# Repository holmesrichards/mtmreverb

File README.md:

# Spring Reverb

This is a Kosmo format adaptation of the [Music Thing Modular Spring Reverb](https://www.musicthing.co.uk/Spring-Reverb/). (Which is open source, [Creative Commons Attribution-ShareAlike 3.0](https://creativecommons.org/licenses/by-sa/3.0/), so this project is too.)

# Circuit changes

Only very minor tweaks to the original circuit:

* Expansion module (consisting of a potentiometer and a pair of RCA jacks) incorporated into main module
* Single rail-to-rail bypass caps replaced with dual rail-to-ground
* Power reversal protection diodes added
* AC coupling capacitors C1, C2 changed from 10 µF electrolytic to 1 µF film
* Footprint for 100k resistor to ground on IN_2 (FEEDBACK) left in place but marked "OMIT?"

# Discussion

R5, the 100k to ground on input IN_2, is parallel to several other ~50k resistances to ground. This means the input impedance at IN_2 is much lower than the usual 100k. R5 only makes it even lower, and I see no reason why one would want to do that. I left the footprint for this resistor in place but marked it "OMIT?" on the silkscreen and left it out in my build. This resistor is not included in the BOM.

# Errata

* In the v1.0 circuit boards the solder jumper is bridged, not open, so it should be cut if using the brick and left alone if not (contrary to what the silkscreen implies). 

* In the v1.0 front panel the pads around the hole for the "To" phono jack make the jack contact ground. This is incorrect. Use nylon washers on both sides of the hole to isolate the jack, and make sure the hole isn't plated through. 

These errors are corrected in the post-v1.0 versions.

## Current draw

 mA +12 V,  mA -12 V
 
## Photos

## Documentation

* [Schematic](Docs/springReverbRev2_schematic.pdf)
* PCB layout: [front board front side](Docs/Layout/springReverbRev2_FrontPCB/springReverbRev2_FrontPCB_front.svg), [front board back side](Docs/Layout/springReverbRev2_FrontPCB/springReverbRev2_FrontPCB_back.svg), [back board front side](Docs/Layout/springReverbRev2_BackPCB/springReverbRev2_BackPCB_front.svg), [back board back side](Docs/Layout/springReverbRev2_BackPCB/springReverbRev2_BackPCB_back.svg)
* [BOM](Docs/BOM/springReverbRev2_bom.md)
* [Blog post](https://analogoutputblog.wordpress.com/2023/05/06/spring-has-sprung/)

## GitHub repository

* [https://github.com/holmesrichards/mtmreverb](https://github.com/holmesrichards/mtmreverb)

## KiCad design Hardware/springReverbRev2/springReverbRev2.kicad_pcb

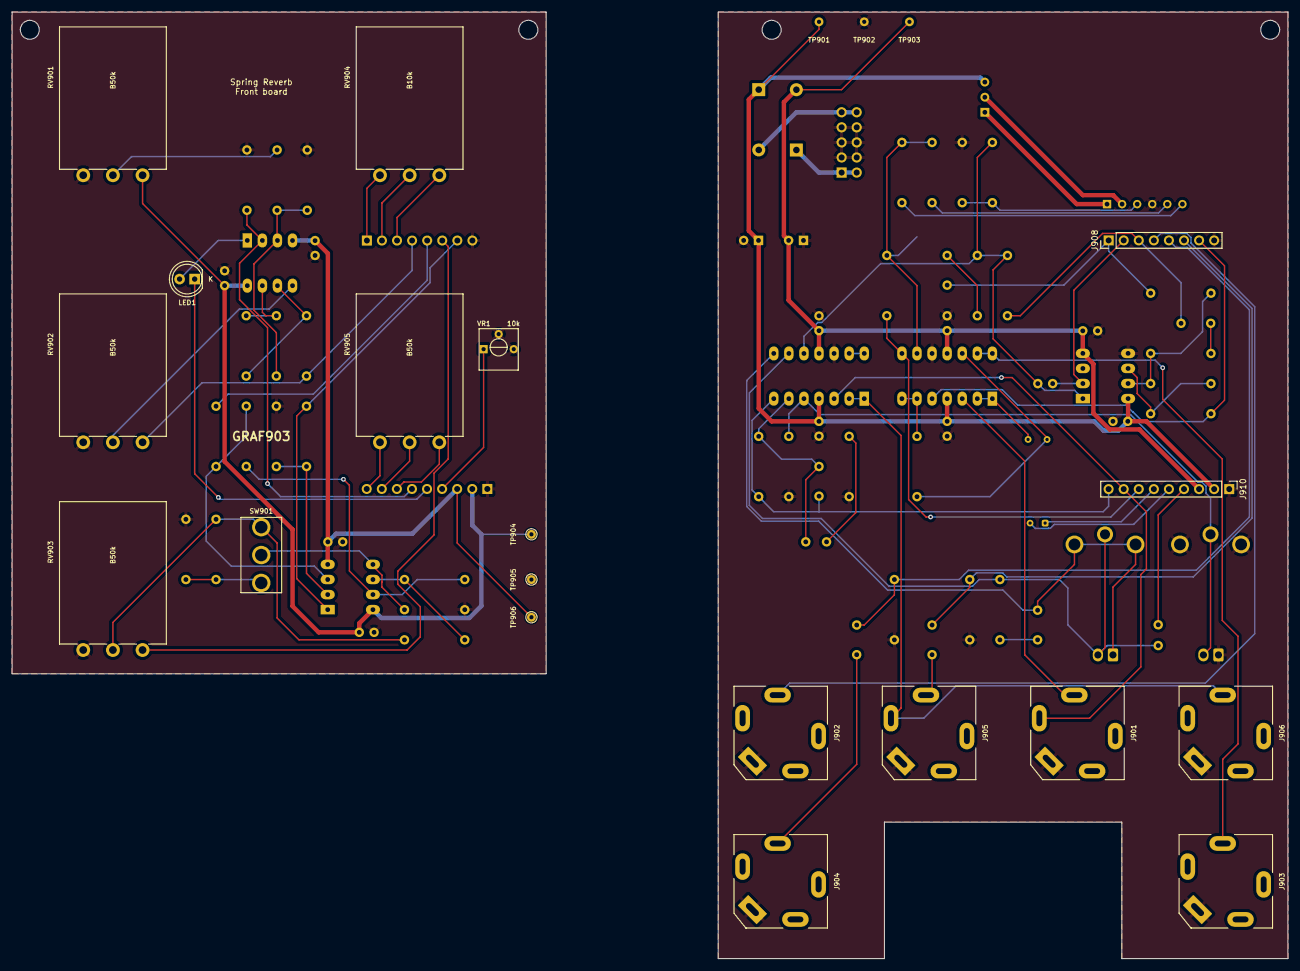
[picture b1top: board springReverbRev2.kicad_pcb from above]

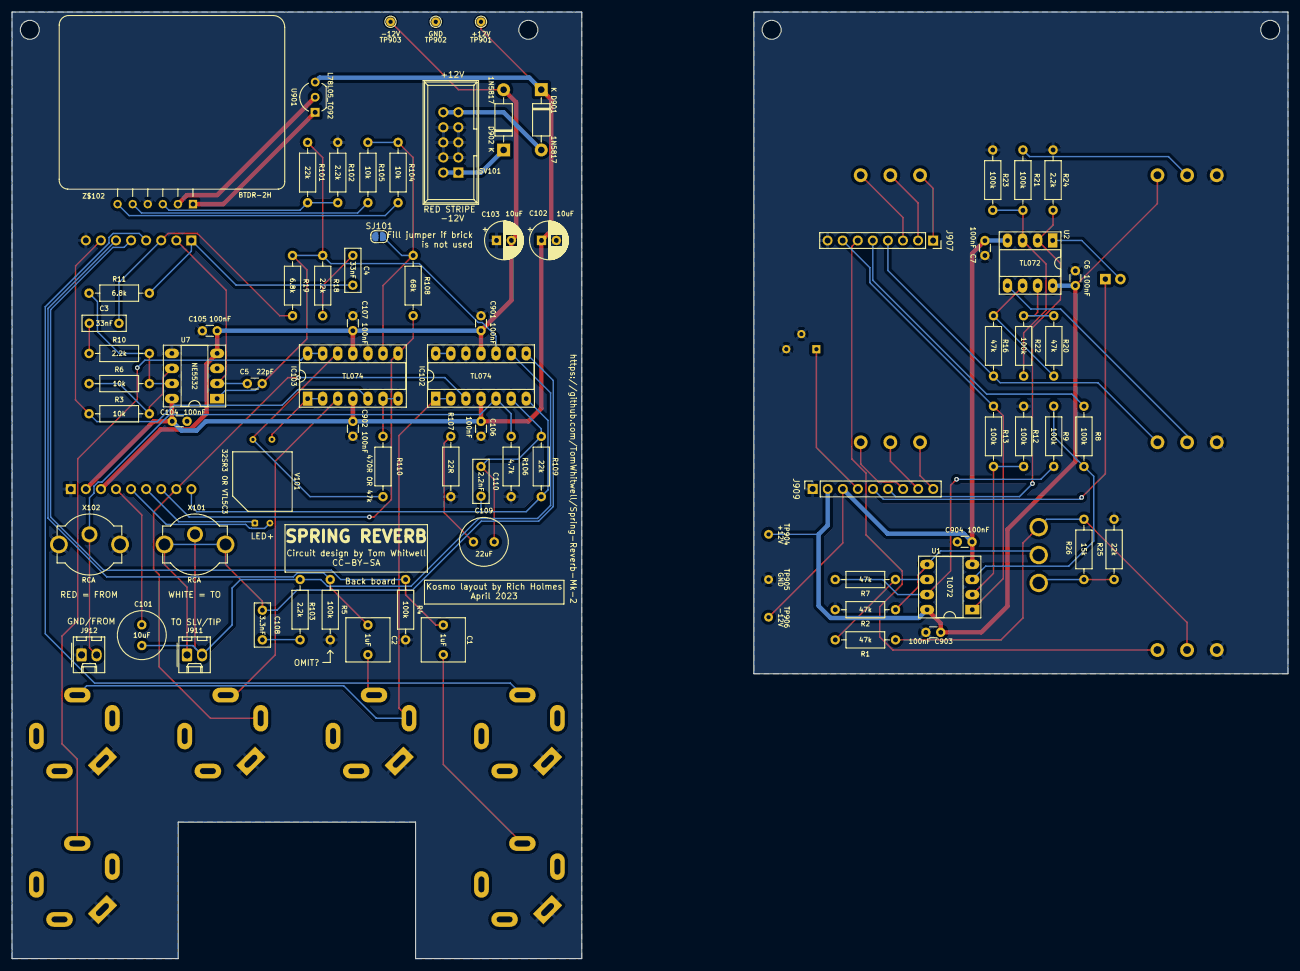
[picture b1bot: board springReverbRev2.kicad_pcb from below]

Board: 2 copper layers, 215.0 x 159.5 mm, 103 parts (75 on the bottom side), 73 nets.

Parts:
B901, B902: Board; Board_Marker
C1, C2: 1uF; C_Rect_L7.2mm_W7.2mm_P5.00mm_FKS2_FKP2_MKS2_MKP2
C3, C4: 33nF; C_Rect_L7.2mm_W2.5mm_P5.00mm_FKS2_FKP2_MKS2_MKP2
C5: 22pF; C_Disc_D3.0mm_W1.6mm_P2.50mm
C6, C7, C104, C105, C106, C107, C901, C902, C903, C904: 100nF; C_Disc_D3.0mm_W1.6mm_P2.50mm
C101: 10uF; C_Radial_D8.0mm_H11.5mm_P3.50mm
C102, C103: 10uF; CP_Radial_D6.3mm_P2.50mm
C108: 3.3nF; C_Rect_L7.2mm_W2.5mm_P5.00mm_FKS2_FKP2_MKS2_MKP2
C109: 22uF; C_Radial_D8.0mm_H11.5mm_P3.50mm
C110: 2.2nF; C_Rect_L7.2mm_W2.5mm_P5.00mm_FKS2_FKP2_MKS2_MKP2
D901, D902: 1N5817; D_DO-41_SOD81_P10.16mm_Horizontal
GRAF901, GRAF902: Holes; springreverb_panel_holes
GRAF903: Holes; springreverb_panel_holes2
H901, H902, H903, H905: MountingHole; MountingHole_3.2mm_M3
IC102, IC103: TL074; DIP-14_W7.62mm_Socket_LongPads
J901, J905: AudioJack2_SwitchT; Jack_6.35mm_PJ_629HAN_slots
J902, J903, J904, J906: AudioJack2; Jack_6.35mm_PJ_629HAN_slots
J907: Conn_01x08_Socket; PinSocket_1x08_P2.54mm_Vertical
J908: Conn_01x08_Pin; PinHeader_1x08_P2.54mm_Vertical
J909: Conn_01x09_Socket; PinSocket_1x09_P2.54mm_Vertical
J910: Conn_01x09_Pin; PinHeader_1x09_P2.54mm_Vertical
J911, J912: 2_pin_Molex_header; Molex_KK-254_AE-6410-02A_1x02_P2.54mm_Vertical
LED1: LED_green; LED_D5.0mm
R1, R2, R7, R16, R20: 47k; R_Axial_DIN0207_L6.3mm_D2.5mm_P10.16mm_Horizontal
R3, R6, R104, R105: 10k; R_Axial_DIN0207_L6.3mm_D2.5mm_P10.16mm_Horizontal
R4, R5, R8, R9, R12, R13, R21, R22, R23: 100k; R_Axial_DIN0207_L6.3mm_D2.5mm_P10.16mm_Horizontal
R10, R18, R24, R102, R103: 2.2k; R_Axial_DIN0207_L6.3mm_D2.5mm_P10.16mm_Horizontal
R11, R19: 6.8k; R_Axial_DIN0207_L6.3mm_D2.5mm_P10.16mm_Horizontal
R25, R101, R109: 22k; R_Axial_DIN0207_L6.3mm_D2.5mm_P10.16mm_Horizontal
R26: 15k; R_Axial_DIN0207_L6.3mm_D2.5mm_P10.16mm_Horizontal
R106: 4.7k; R_Axial_DIN0207_L6.3mm_D2.5mm_P10.16mm_Horizontal
R107: 22R; R_Axial_DIN0207_L6.3mm_D2.5mm_P10.16mm_Horizontal
R108: 68k; R_Axial_DIN0207_L6.3mm_D2.5mm_P10.16mm_Horizontal
R110: 470R OR 47k; R_Axial_DIN0207_L6.3mm_D2.5mm_P10.16mm_Horizontal
RV901, RV902, RV903, RV905: B50k; Potentiometer_Alpha_16mm_Single_Vertical
RV904: B10k; Potentiometer_Alpha_16mm_Single_Vertical
SJ101: SolderJumper; SolderJumper-2_P1.3mm_Open_RoundedPad1.0x1.5mm
SV101: Synth_power_2x5; Power_Header
SW901: SW_SPDT_MSM; SPDT-toggle-switch-1M-series
TP901, TP904: +12V; TestPoint_THTPad_D1.5mm_Drill0.7mm
TP902, TP905: GND; TestPoint_THTPad_D1.5mm_Drill0.7mm
TP903, TP906: -12V; TestPoint_THTPad_D1.5mm_Drill0.7mm
U1, U2: TL072; DIP-8_W7.62mm_Socket_LongPads
U7: NE5532; DIP-8_W7.62mm_Socket_LongPads
U901: L78L05_TO92; TO-92_Inline_Wide
V101: 32SR3 OR VTL5C3; Vactrol_VTL5C
VR1: 10k; Potentiometer_Bourns_3362P_Vertical_screw_centered
X101: RCA; RCJ-023 white
X102: RCA; RCJ-022 red
Z$102: BTDR-2H

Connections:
+5V: U901.1 (VO), Z$102.1 (+5VDC)
+12V: C6.1, C903.1, J909.2, RV901.3, TP904.1, U1.8 (V+), U2.8 (V+)
+12V_B: C102.1, C104.1, C106.1, C902.1, D901.1 (K), IC102.4 (V+), IC103.4 (V+), J910.2, TP901.1, U7.8 (V+), U901.3 (VI)
-12V: C7.2, C904.2, J909.3, TP906.1, U1.4 (V-), U2.4 (V-)
-12V_B: C103.2, C105.2, C107.2, C901.2, D902.2 (A), IC102.11 (V-), IC103.11 (V-), J910.3, TP903.1, U7.4 (V-)
/+12V_INLET: D901.2 (A), SV101.9 (+12V), SV101.10 (+12V)
/-12V_INLET: D902.1 (K), SV101.1 (-12V), SV101.2 (-12V)
/Back board/AUDIO_IN_1: C1.1, J908.5, R4.1
/Back board/AUDIO_IN_2: C2.1, J908.6, R5.1
/Back board/CV_IN: J902.T, J908.4
/Back board/DRY_B: IC103.5 (+), J908.7, R3.1
/Back board/EQ_POT_1_B: C4.1, J908.1, R11.2
/Back board/EQ_POT_2_B: C5.1, J908.2, U7.2 (-)
/Back board/EQ_POT_3_B: C3.2, J908.3, R19.1
/Back board/FROM_TANK: IC102.5 (+), J912.2, R106.1, X102.T
/Back board/IN_1: C1.2, J904.T
/Back board/IN_2: C2.2, J905.T
/Back board/MIX: IC103.13 (-), IC103.14, J903.T
/Back board/MIXPOT_BRICK_B: IC103.8, J910.7, R108.2
/Back board/MIXPOT_SPRING_B: C110.2, IC102.7, J910.9, R109.2
/Back board/PWR_GND: U901.2 (GND), Z$102.2 (PWR-GND)
/Back board/REVERB_RETURN: IC102.3 (+), J901.TN, J910.8
/Back board/REVERB_SEND: C5.2, IC102.10 (+), R18.2, R19.2, R101.1, U7.1
/Back board/TO_TANK: C101.1, IC102.9 (-), J911.2, R103.2, X101.T
/Back board/TO_TANK_S_B: C108.1, IC102.8, J911.1, X101.S
/Back board/TRIM_B: C101.2, J910.4
/Back board/VAC_AN_B: J910.5, V101.2 (+)
/Back board/VAC_CA_B: J910.6, V101.1 (-)
/Back board/WET: IC102.1, IC102.2 (-), J905.TN, J906.T
/Back board/XFADE: IC103.3 (+), J901.T
/Front board/AUDIO_IN_1: J907.5, R8.1
/Front board/AUDIO_IN_2: J907.6, RV903.3
/Front board/CV_IN: J907.4, R16.1, RV902.3
/Front board/CV_LEVEL: RV902.2, U2.5 (+)
/Front board/DRY_F: J907.7, R13.2, U1.1
/Front board/EQ_POT_1_F: J907.1, RV904.1
/Front board/EQ_POT_2_F: J907.2, RV904.2
/Front board/EQ_POT_3_F: J907.3, RV904.3
/Front board/FB_LEVEL: R1.1, R26.1, RV903.2, SW901.3
/Front board/MIX: R21.1, RV901.2
/Front board/MIXPOT_BRICK_F: J909.7, RV905.3
/Front board/MIXPOT_SB_MIX_F: J909.8, RV905.2
/Front board/MIXPOT_SPRING_F: J909.9, RV905.1
/Front board/TRIM_F: J909.4, VR1.1
/Front board/VAC_AN_F: J909.5, LED1.1 (K)
/Front board/VAC_CA_F: J909.6, R24.1, U2.2 (-)
GND: C6.2, C7.1, C903.2, C904.1, J907.8, J909.1, R2.2, R12.2, R23.2, R24.2, R25.2, RV901.1, RV902.1, RV903.1, TP905.1, VR1.2, VR1.3
GND_B: C102.2, C103.1, C104.2, C105.1, C106.2, C107.1, C901.1, C902.2, IC102.12 (+), IC103.10 (+), J901.S, J902.S, J903.S, J904.S, J905.S, J906.S, J908.8, J910.1, J912.1, R4.2, R5.2, R102.2, R106.2, R107.2, SJ101.1 (A), SV101.3 (GND), SV101.4 (GND), SV101.5 (GND), SV101.6 (GND), SV101.7 (GND), SV101.8 (GND), TP902.1, U7.3 (+), U7.5 (+), X102.S, Z$102.4 (SIG-GND)
unnamed: C3.1, R10.2
unnamed: C4.2, R18.1
unnamed: C108.2, R103.1
unnamed: C109.1, R107.1
unnamed: C109.2, C110.1, IC102.6 (-), R109.1
unnamed: IC102.13 (-), IC102.14
unnamed: IC103.1, IC103.2 (-), V101.4
unnamed: IC103.6 (-), IC103.7, R110.2
unnamed: IC103.9 (-), R104.2, R105.2, R108.1, SJ101.2 (B)
unnamed: IC103.12 (+), R110.1, V101.3
unnamed: LED1.2 (A), U2.1
unnamed: R7.2, R9.1, U1.7
unnamed: R6.2, R10.1, R11.1, U7.7
unnamed: R20.2, R22.1, U2.7
unnamed: R25.1, R26.2, SW901.1
unnamed: R8.2, R9.2, U1.3 (+)
unnamed: R12.1, R13.1, U1.2 (-)
unnamed: R2.1, SW901.2, U1.5 (+)
unnamed: R1.2, R7.1, U1.6 (-)
unnamed: R21.2, R22.2, R23.1, U2.3 (+)
unnamed: R16.2, R20.1, U2.6 (-)
unnamed: R3.2, R6.1, U7.6 (-)
unnamed: R101.2, R102.1, Z$102.3 (INPUT)
unnamed: R104.1, Z$102.6 (OUT1)
unnamed: R105.1, Z$102.5 (OUT2)

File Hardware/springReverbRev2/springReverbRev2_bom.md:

# springReverbRev2.kicad_sch BOM

Wed 08 Mar 2023 10:55:59 PM EST

Generated from schematic by Eeschema 7.0.0-da2b9df05c~171~ubuntu22.04.1

**Component Count:** 109

| Refs | Qty | Component | Description | Manufacturer | Part | Vendor | SKU |
| ----- | --- | ---- | ----------- | ---- | ---- | ---- | ---- |
| C1, C2, C101 | 3 | 10uF | Unpolarized electrolytic capacitor |  |  | Tayda |  |
| C3, C4 | 2 | 33nF | Polyester film capacitor |  |  | Tayda |  |
| C5 | 1 | 22pF | Ceramic capacitor |  |  | Tayda |  |
| C6, C7, C104–107, C901–904 | 10 | 100nF | Ceramic capacitor |  |  | Tayda |  |
| C102, C103 | 2 | 10uF | Electrolytic capacitor, 2.5 mm pitch |  |  | Tayda | A-4349 |
| C108 | 1 | 3.3nF | Polyester film capacitor |  |  | Tayda |  |
| C109 | 1 | 22uF | Unpolarized electrolytic capacitor |  |  | Tayda |  |
| C110 | 1 | 2.2nF | Polyester film capacitor |  |  | Tayda |  |
| D901, D902 | 2 | 1N5817 | Schottky Barrier Rectifier Diode, DO-41 |  |  | Tayda | A-159 |
| IC102, IC103 | 2 | TL074 | Quad operational amplifier, DIP-14 |  |  | Tayda | A-1138 |
| J901, J905 | 2 | AudioJack2_SwitchT | Audio Jack, 2 Poles (Mono / TS), Switched T Pole (Normalling) |  |  | Tayda | A-1121 |
| J902–904, J906 | 4 | AudioJack2 | Audio Jack, 2 Poles (Mono / TS) |  |  | Tayda | A-1121 |
| J907 | 1 | Conn_01x08_Socket | Generic connector, single row, 01x08, script generated |  |  |  |  |
| J908 | 1 | Conn_01x08_Pin | Generic connector, single row, 01x08, script generated |  |  |  |  |
| J909 | 1 | Conn_01x09_Socket | Generic connector, single row, 01x09, script generated |  |  |  |  |
| J910 | 1 | Conn_01x09_Pin | Generic connector, single row, 01x09, script generated |  |  |  |  |
| J911, J912 | 2 | 2_pin_Molex_header | KK254 Molex header |  |  | Tayda | A-804 |
| J913, J914 | 2 | 2_pin_Molex_connector | KK254 Molex connector |  |  | Tayda | A-826 |
| J915–917 | 3 | DIP-8 | 8 pin DIP socket |  |  |  |  |
| J918, J919 | 2 | DIP-14 | 14 pin DIP socket |  |  |  |  |
| LED1 | 1 | LED_green | Light emitting diode |  |  | Tayda | A-1553 |
| R1, R2, R7, R16, R20 | 5 | 47k | Resistor |  |  | Tayda |  |
| R3, R6, R104, R105 | 4 | 10k | Resistor |  |  | Tayda |  |
| R8, R9, R12, R13, R21–23, R901, R902 | 9 | 100k | Resistor |  |  | Tayda |  |
| R10, R18, R24, R102, R103 | 5 | 2.2k | Resistor |  |  | Tayda |  |
| R11, R19 | 2 | 6.8k | Resistor |  |  | Tayda |  |
| R25, R101, R109 | 3 | 22k | Resistor |  |  | Tayda |  |
| R26 | 1 | 15k | Resistor |  |  | Tayda |  |
| R106 | 1 | 4.7k | Resistor |  |  | Tayda |  |
| R107 | 1 | 22R | Resistor |  |  | Tayda |  |
| R108 | 1 | 68k | Resistor |  |  | Tayda |  |
| R110 | 1 | 470R OR 47k | Resistor |  |  | Tayda |  |
| RV901–903, RV905 | 4 | B50k | Potentiometer |  |  | Tayda |  |
| RV904 | 1 | B10k | Potentiometer |  |  | Tayda |  |
| SV101 | 1 | Synth_power_2x5 | Pin header 2.54 mm 2x5 |  |  | Tayda | A-2939 |
| SW901 | 1 | SW_SPDT_MSM | Switch, single pole double throw, center OFF position |  |  | Tayda | A-3187 |
| U1, U2 | 2 | TL072 | Dual operational amplifier, DIP-8 |  |  | Tayda | A-037 |
| U7 | 1 | NE5532 | Dual Low-Noise Operational Amplifiers, DIP-8/SOIC-8 |  |  |  |  |
| U901 | 1 | L78L05_TO92 | Positive 100mA 30V Linear Regulator, Fixed Output 5V, TO-92 |  |  | Tayda | A-176 |
| V101 | 1 | 32SR3 OR VTL5C3 | Low Cost Axial Vactrols |  |  |  |  |
| VR1 | 1 | 10k | Trim-potentiometer |  |  | Tayda |  |
| X101 | 1 | RCA | Audio Jack, 2 Poles (Mono / TS) | CUI | RCJ-023 | Digi-Key | CP-1408-ND |
| X102 | 1 | RCA | Audio Jack, 2 Poles (Mono / TS) | CUI | RCJ-022 | Digi-Key | CP-1407-ND |
| X103 | 1 | RCA | Audio Jack, 2 Poles (Mono / TS) | Switchcraft | BPJF03X | Digi-Key | SC2441-ND |
| X104 | 1 | RCA | Audio Jack, 2 Poles (Mono / TS) | Switchcraft | BPJF02X | Digi-Key | SC2439-ND |
| Z$102 | 1 | BTDR-2H |  |  |  |  |  |
| ZKN901 | 1 | Knob_MF-A04 | MF-A04 knob |  |  |  |  |
| ZKN902 | 1 | Knob_MF-A03 | MF-A03 knob |  |  |  |  |
| ZKN903–905 | 3 | Knob_MF-A01 | MF-A01 knob |  |  |  |  |
| ZSC901–904 | 4 | Screw | M3 6 mm screw |  |  |  |  |
| ZSP901, ZSP902 | 2 | Spacer | M3 10 mm FF spacer |  |  |  |  |
| ZWA901, ZWA902 | 2 | Washer | M3 washer |  |  |  |  |

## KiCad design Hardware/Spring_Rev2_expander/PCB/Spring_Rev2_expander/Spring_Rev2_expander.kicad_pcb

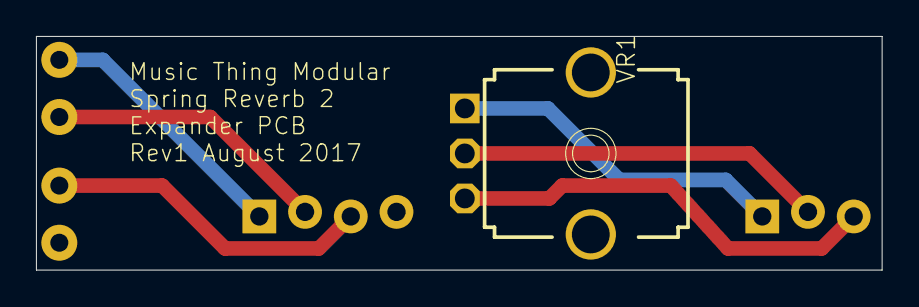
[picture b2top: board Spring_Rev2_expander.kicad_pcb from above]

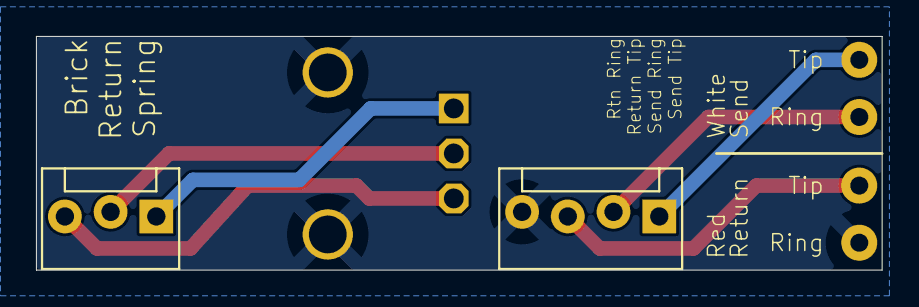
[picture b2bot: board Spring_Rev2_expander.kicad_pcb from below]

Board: 2 copper layers, 47.0 x 13.0 mm, 7 parts (6 on the bottom side), 7 nets.

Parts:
JP1: MOLEX-1X3_LOCK
JP2: MOLEX-1X4_LOCK
RETURN-RED-RING0: PAD-1.00-2.00
RETURN-RED-TIP0: PAD-1.00-2.00
SEND-WHITE-RING0: PAD-1.00-2.00
SEND-WHITE-TIP0: PAD-1.00-2.00
VR1: 9MM_SNAP-IN_POT

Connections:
BRICK: JP1.3, VR1.3
GND: JP2.4, RETURN-RED-RING0.1, VR1.CHASSIS1, VR1.CHASSIS2
OUT: JP1.2, VR1.2
R+: JP2.3, RETURN-RED-TIP0.1
S+: JP2.1, SEND-WHITE-TIP0.1
S-: JP2.2, SEND-WHITE-RING0.1
SPRING: JP1.1, VR1.1

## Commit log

2022-06-11 Initial version
2022-06-12 Note on phono jacks, replace pin headers with Molex
2022-06-12 Layout redone
2022-06-12 phono jacks
2022-06-14 Reorg folders
2022-08-19 panel
2022-09-22 Schem tidying
2022-11-12 misc corrections
2023-02-16 Backlog
2023-02-16 Bigger tone knob; hardware
2023-02-22 libraries in new place
2023-03-08 rm submodules
2023-03-08 rm expander, reorg PCB folder
2023-03-09 Docs
2023-03-13 reorg
2023-03-17 PCB revisions, Docs
2023-03-29 Restore R4 and R5 references; change C1 and C2 values; mark R5 to omit; README list of changes
2023-05-05 Docs; make LED position consistent
2023-05-05 Panel image
2023-05-05 Use open not bridged jumper
2023-05-05 README update
2023-05-06 License
2023-05-06 Correct mix pot label
2023-05-17 Ungrounded jack for tank send
2023-05-17 Link to MTM
2023-05-18 Ungrounded jack
2023-05-18 Photos
2023-06-04 License corrected to CC-BY-SA
